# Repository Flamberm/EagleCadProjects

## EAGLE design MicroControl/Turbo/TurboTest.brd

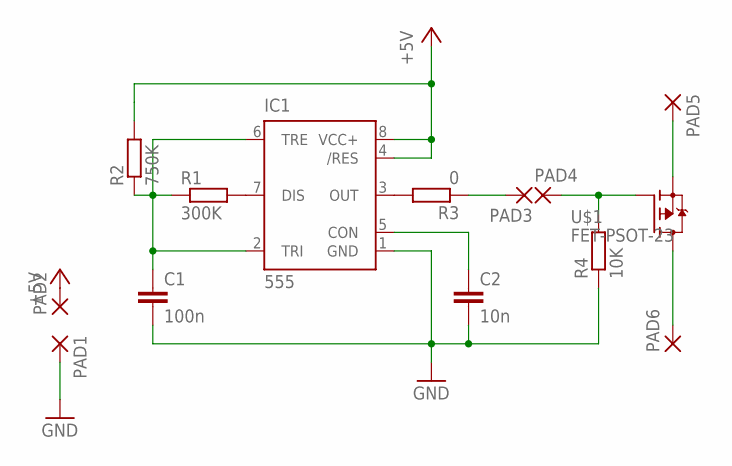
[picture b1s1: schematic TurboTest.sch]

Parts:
C1: 100n; CAP0805
C2: 10n; CAP0805
IC1: 555; SOIC-8
PAD1, PAD2, PAD3, PAD4, PAD5, PAD6: WIREPAD-SMD2; PAD-1.27X2.54
R1: 300K; RESC2012X50
R2: 750K; RESC2012X50
R3: 0; RESC2012X50
R4: 10K; RESC2012X50
U$1: FET-PSOT-23; SOT95P240X115-3

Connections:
+5V: IC1.4 (/RES), IC1.8 (VCC+), PAD2.P$1, R2.2
GND: C1.2, C2.2, IC1.1 (GND), PAD1.P$1, R4.1
unnamed: IC1.7 (DIS), R1.2
unnamed: C1.1, IC1.2 (TRI), IC1.6 (TRE), R1.1, R2.1
unnamed: C2.1, IC1.5 (CON)
unnamed: IC1.3 (OUT), R3.2
unnamed: PAD3.P$1, R3.1
unnamed: PAD4.P$1, R4.2, U$1.1 (G)
unnamed: PAD5.P$1, U$1.2 (S)
unnamed: PAD6.P$1, U$1.3 (D)

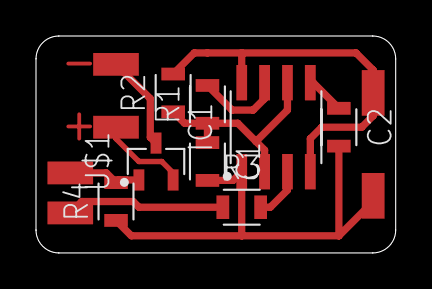
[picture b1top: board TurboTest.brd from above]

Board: 2 copper layers, 20.0 x 12.1 mm, 14 parts (0 on the bottom side), 10 nets.

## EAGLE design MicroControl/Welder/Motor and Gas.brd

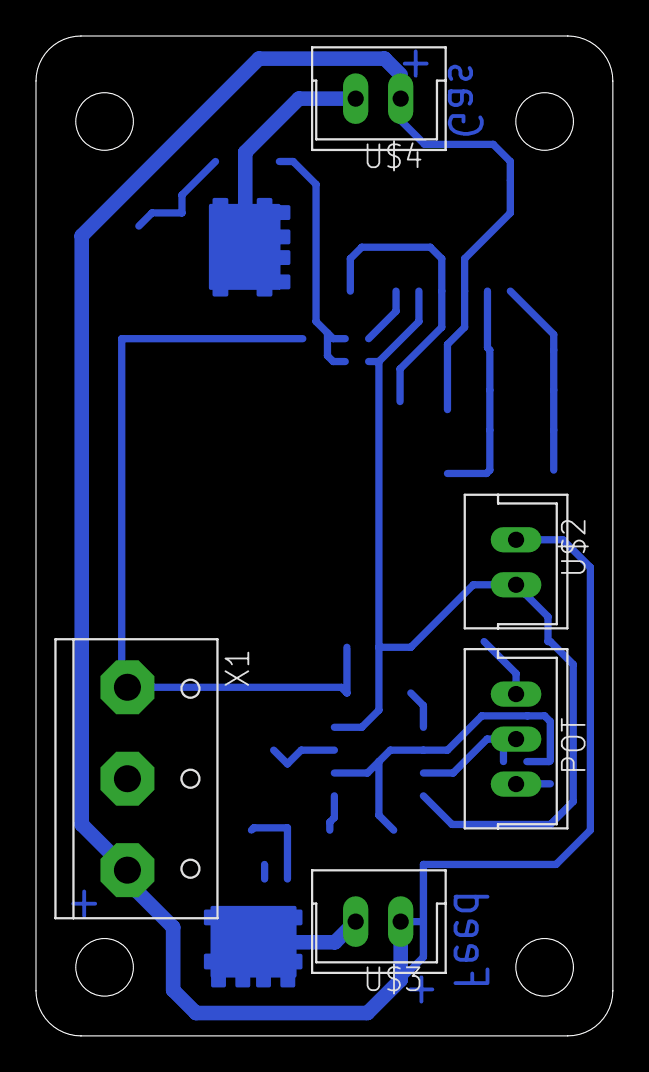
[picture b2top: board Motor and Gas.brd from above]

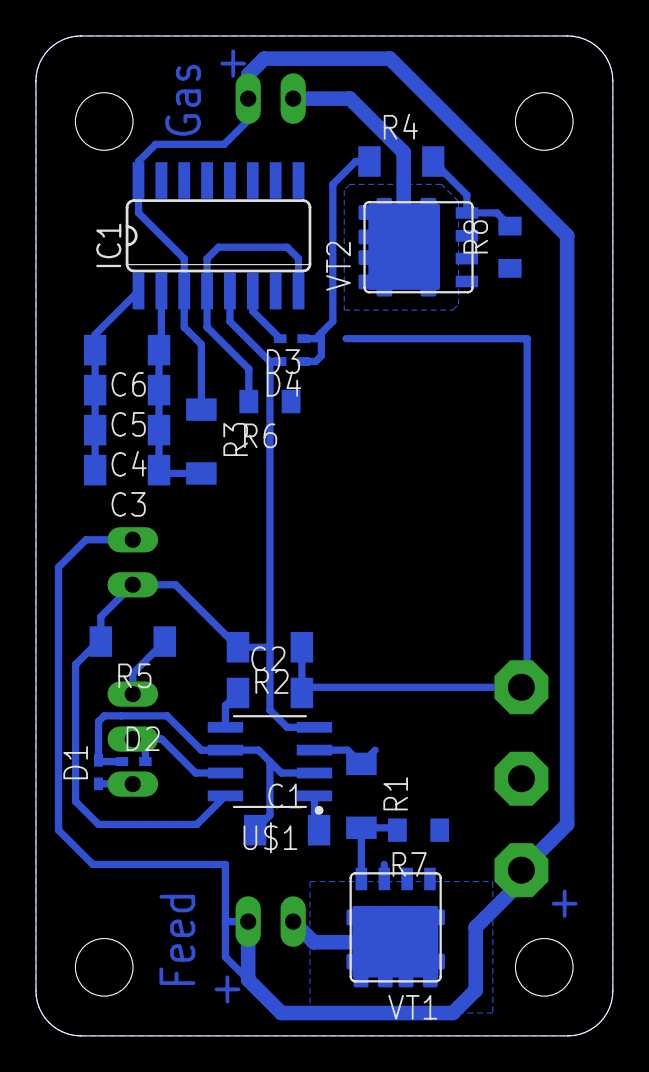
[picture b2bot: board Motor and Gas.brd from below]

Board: 2 copper layers, 32.0 x 55.5 mm, 27 parts (22 on the bottom side), 18 nets.

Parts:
C1: 1n; C1206
C2, C3, C4, C5, C6: 1u; C1206
D1, D2, D3, D4: SOD523
IC1: 4098D; SO16
POT: CON-XH-03; XH-03
R1, R4: 51R; R1206
R2: 10k; R1206
R3: 1M; R1206
R5: 390R; R1206
R6: R0805
R7, R8: 1K; R0805
U$1: IC-555SO-8; SOIC127P600X175-8
U$2, U$3, U$4: CON-XH-02; XH-02
VT1, VT2: POWERFLAT-5X6
X1: CON-5.08-03P; MKDSN1,5/3-5,08

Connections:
+12V: IC1.3, IC1.16, R3.1, U$2.1, U$3.1, U$4.1, X1.3
GND: C1.2, C2.2, R2.1, R6.1, R7.1, R8.1, U$1.1, VT1.S1, VT1.S2, VT1.S3, VT2.S1, VT2.S2, VT2.S3, X1.1
unnamed: U$3.2, VT1.D1
unnamed: C1.1, D1.A, D2.C, U$1.2, U$1.6
unnamed: C2.1, U$1.5
unnamed: D2.A, POT.2, U$1.7
unnamed: D1.C, POT.3
unnamed: POT.1, R5.1
unnamed: R1.1, U$1.3
unnamed: R1.2, R7.2, VT1.G
unnamed: D4.A, IC1.5, R2.2, R5.2, U$1.4, U$1.8, U$2.2
unnamed: C3.2, C4.2, C5.2, C6.2, IC1.1
unnamed: C3.1, C4.1, C5.1, C6.1, IC1.2, R3.2
unnamed: D3.A, IC1.6
unnamed: R4.2, R8.2, VT2.G
unnamed: IC1.4, IC1.8, R6.2
unnamed: U$4.2, VT2.D1
unnamed: D3.C, D4.C, R4.1

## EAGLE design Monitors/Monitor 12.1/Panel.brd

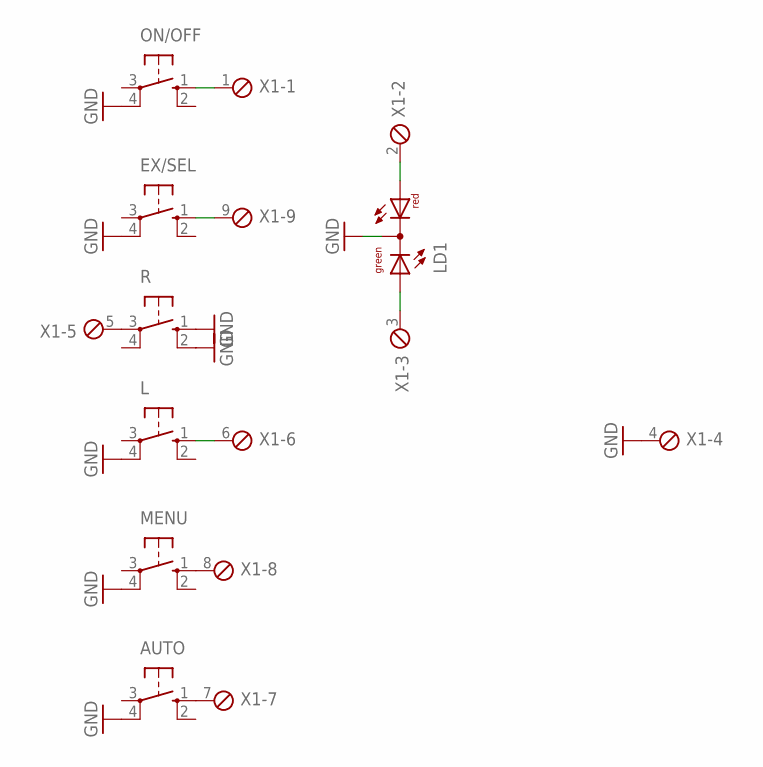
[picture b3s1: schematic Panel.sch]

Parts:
AUTO: 10-XX; B3F-10XX
EX/SEL: 10-XX; B3F-10XX
L: 10-XX; B3F-10XX
LD1: DUOLED-RG-C; DUOLED-C-5MM
MENU: 10-XX; B3F-10XX
ON/OFF: 10-XX; B3F-10XX
R: 10-XX; B3F-10XX
X1: MPT9; 9POL254

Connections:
GND: AUTO.4 (P1), EX/SEL.4 (P1), L.4 (P1), LD1.C, MENU.4 (P1), ON/OFF.4 (P1), R.1 (S), R.2 (S1), X1.4
unnamed: ON/OFF.1 (S), X1.1
unnamed: LD1.AR, X1.2
unnamed: LD1.AX (AG), X1.3
unnamed: EX/SEL.1 (S), X1.9
unnamed: R.3, X1.5
unnamed: L.1 (S), X1.6
unnamed: MENU.1 (S), X1.8
unnamed: AUTO.1 (S), X1.7

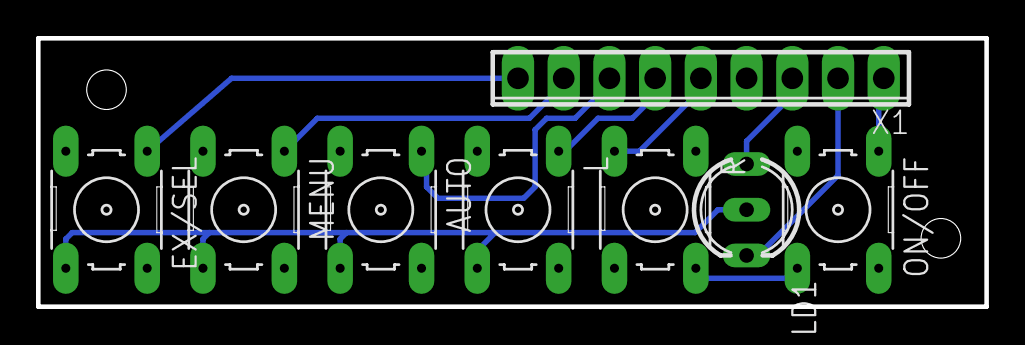
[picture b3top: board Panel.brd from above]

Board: 2 copper layers, 52.7 x 14.9 mm, 8 parts (0 on the bottom side), 9 nets.

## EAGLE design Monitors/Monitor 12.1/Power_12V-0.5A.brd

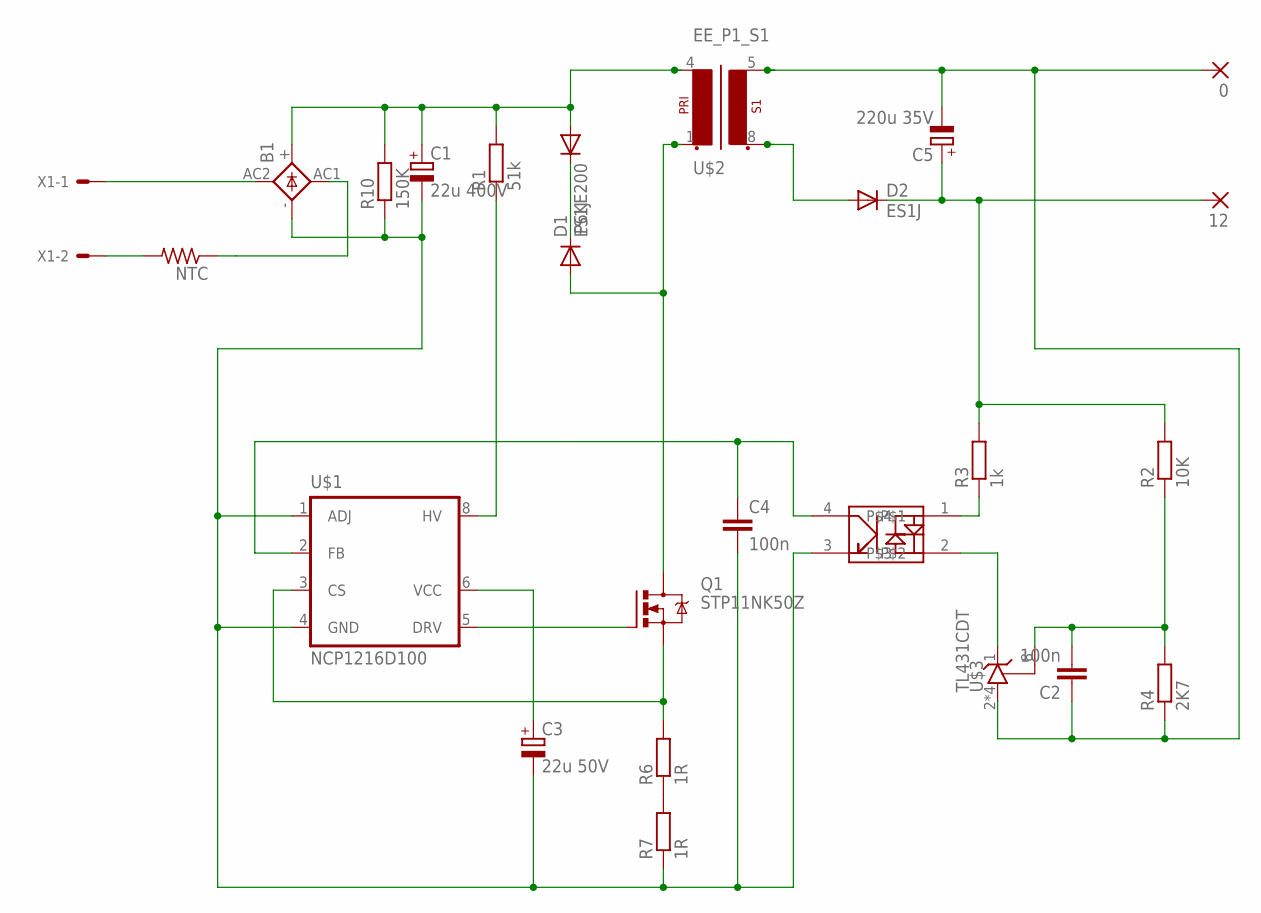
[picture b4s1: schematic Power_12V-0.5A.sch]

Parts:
0, 12: 2,54/0,8
B1: KBL
C1: 22u 400V; E5-13
C2, C4: 100n; C1206
C3: 22u 50V; E2,5-5
C5: 220u 35V; E2,5-7
D1, D2: ES1J; DO-214AC
NTC: R-US_0207/10; 0207/10
P6KE200: DIODE-SMB; SMB
Q1: STP11NK50Z; TO220BV
R1: 51k; 0922/22
R2: 10K; R1206
R3: 1k; R1206
R4: 2K7; R1206
R6, R7: 1R; R1206
R10: 150K; 0204/7
U$1: NCP1216D100; SOP8
U$2: EE_P1_S1; EE25_P1_S1
U$3: TL431CDT; SO8
U$5: EL3H4(TA)-VG; SSOP4
X1: KK-156-2

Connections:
unnamed: NTC.2, X1.2
unnamed: B1.AC2 (AC1), X1.1
unnamed: B1.AC1 (AC2), NTC.1
unnamed: R6.1, R7.2
unnamed: C4.1, U$1.2 (FB), U$5.4
unnamed: B1.+, C1.+, P6KE200.A, R1.2, R10.2, U$2.4 (P1-2)
unnamed: D1.C, P6KE200.C
unnamed: D1.A, Q1.D, U$2.1 (P1-1)
unnamed: C2.2, R2.1, R4.2, U$3.8 (R)
unnamed: R1.1, U$1.8 (HV)
unnamed: Q1.G, U$1.5 (DRV)
unnamed: Q1.S, R6.2, U$1.3 (CS)
unnamed: R3.1, U$5.1
unnamed: C3.+, U$1.6 (VCC)
unnamed: U$3.1 (C), U$5.2
unnamed: B1.-, C1.-, C3.-, C4.2, R7.1, R10.1, U$1.1 (ADJ), U$1.4 (GND), U$5.3
unnamed: 0.1, C2.1, C5.-, R4.1, U$2.5 (S1-2), U$3.2 (A), U$3.3 (A), U$3.6 (A), U$3.7 (A)
unnamed: 12.1, C5.+, D2.C, R2.2, R3.2
unnamed: D2.A, U$2.8 (S1-1)

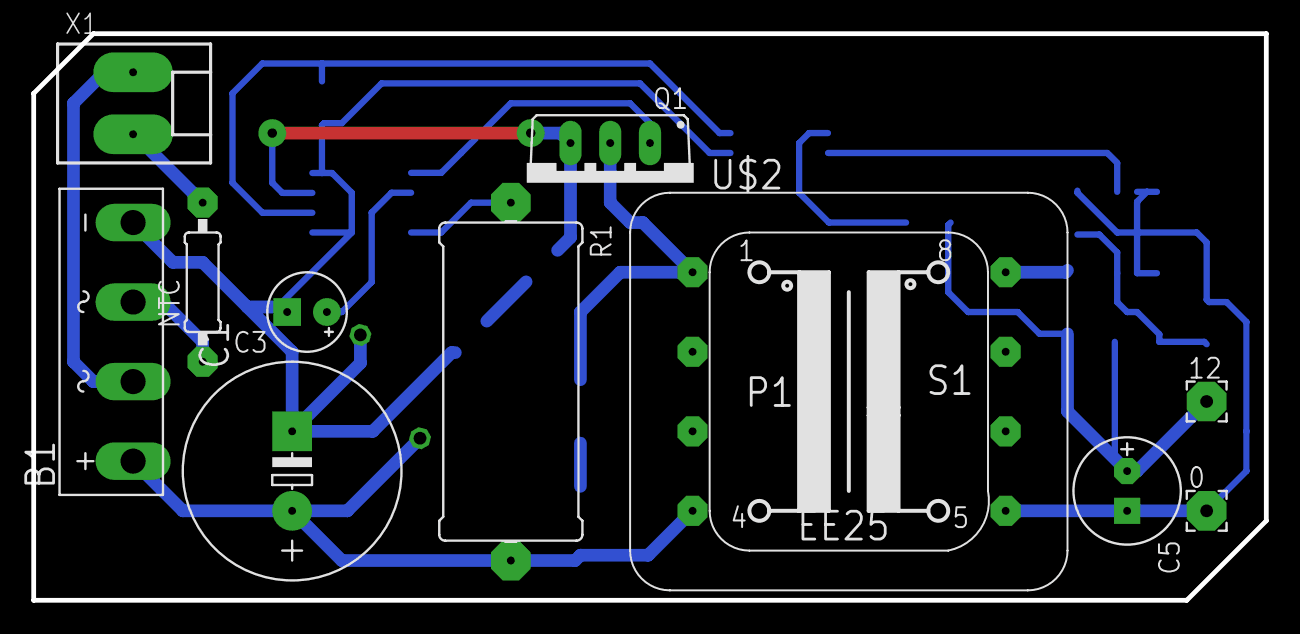
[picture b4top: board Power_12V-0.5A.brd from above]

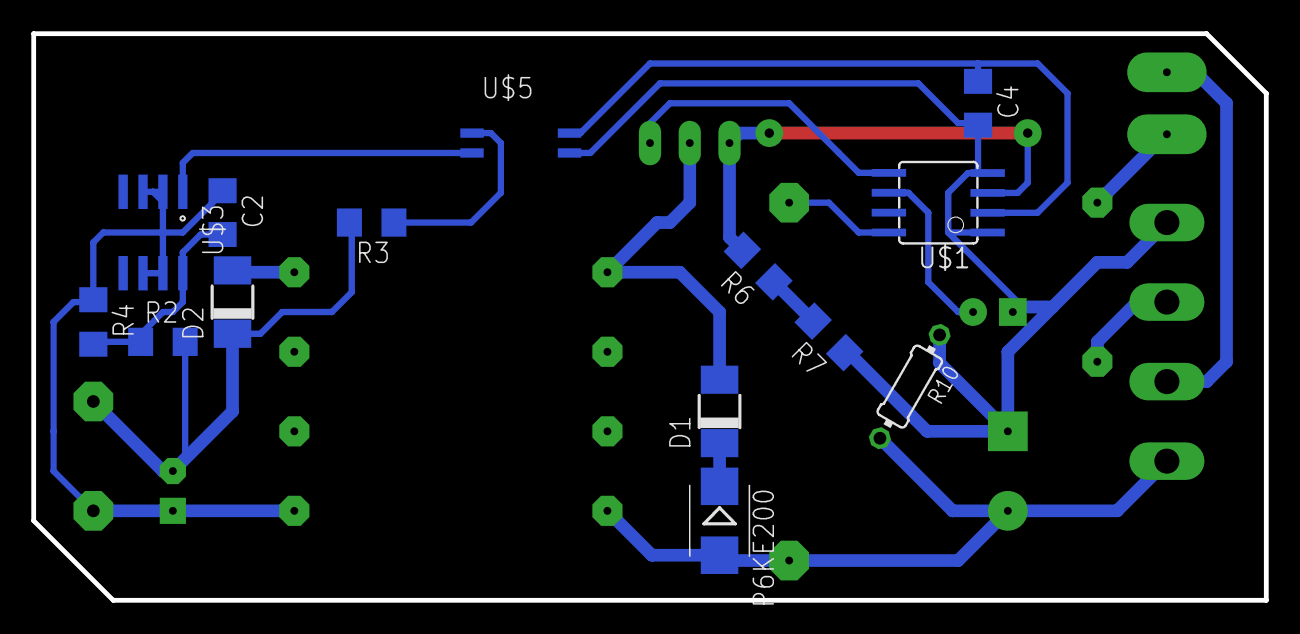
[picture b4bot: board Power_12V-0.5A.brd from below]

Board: 2 copper layers, 78.7 x 36.2 mm, 25 parts (14 on the bottom side), 19 nets.

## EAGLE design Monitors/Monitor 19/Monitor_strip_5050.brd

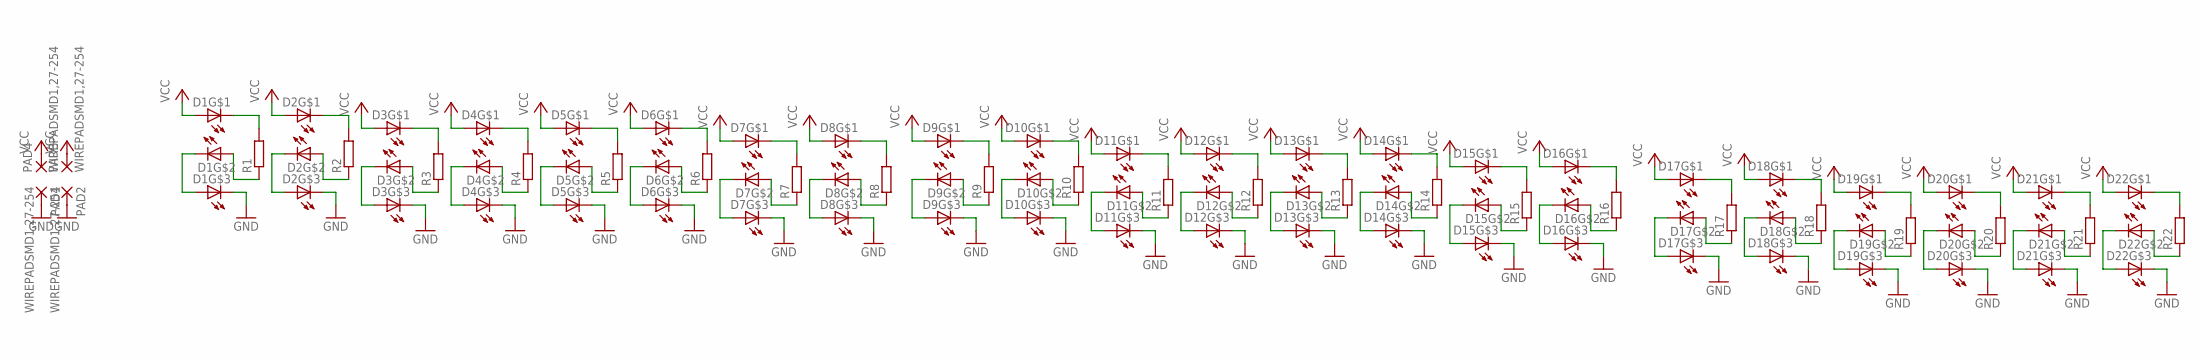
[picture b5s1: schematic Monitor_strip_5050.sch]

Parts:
D1, D2, D3, D4, D5, D6, D7, D8, D9, D10, D11, D12, D13, D14, D15, D16, D17, D18, D19, D20, D21, D22: LED5050_SEPARATES; LED505_SMALLPADS
PAD1, PAD2, PAD3, PAD4: WIREPADSMD1,27-254; SMD1,27-2,54
R1, R2, R3, R4, R5, R6, R7, R8, R9, R10, R11, R12, R13, R14, R15, R16, R17, R18, R19, R20, R21, R22: R-EU_R0805; R0805

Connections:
GND: D1.P$3 (C), D2.P$3 (C), D3.P$3 (C), D4.P$3 (C), D5.P$3 (C), D6.P$3 (C), D7.P$3 (C), D8.P$3 (C), D9.P$3 (C), D10.P$3 (C), D11.P$3 (C), D12.P$3 (C), D13.P$3 (C), D14.P$3 (C), D15.P$3 (C), D16.P$3 (C), D17.P$3 (C), D18.P$3 (C), D19.P$3 (C), D20.P$3 (C), D21.P$3 (C), D22.P$3 (C), PAD1.1, PAD2.1
unnamed: D1.P$1 (C), R1.2
unnamed: D1.P$5 (A), R1.1
unnamed: D2.P$2 (C), D2.P$4 (A)
unnamed: D2.P$1 (C), R2.2
unnamed: D2.P$5 (A), R2.1
unnamed: D3.P$2 (C), D3.P$4 (A)
unnamed: D3.P$1 (C), R3.2
unnamed: D3.P$5 (A), R3.1
unnamed: D4.P$2 (C), D4.P$4 (A)
unnamed: D1.P$2 (C), D1.P$4 (A)
unnamed: D4.P$1 (C), R4.2
unnamed: D4.P$5 (A), R4.1
unnamed: D5.P$2 (C), D5.P$4 (A)
unnamed: D5.P$1 (C), R5.2
unnamed: D5.P$5 (A), R5.1
unnamed: D6.P$2 (C), D6.P$4 (A)
unnamed: D6.P$1 (C), R6.2
unnamed: D6.P$5 (A), R6.1
unnamed: D7.P$2 (C), D7.P$4 (A)
unnamed: D7.P$1 (C), R7.2
unnamed: D7.P$5 (A), R7.1
unnamed: D8.P$2 (C), D8.P$4 (A)
unnamed: D8.P$1 (C), R8.2
unnamed: D8.P$5 (A), R8.1
unnamed: D9.P$2 (C), D9.P$4 (A)
unnamed: D9.P$1 (C), R9.2
unnamed: D9.P$5 (A), R9.1
unnamed: D10.P$2 (C), D10.P$4 (A)
unnamed: D10.P$1 (C), R10.2
unnamed: D10.P$5 (A), R10.1
unnamed: D11.P$2 (C), D11.P$4 (A)
unnamed: D11.P$1 (C), R11.2
unnamed: D11.P$5 (A), R11.1
unnamed: D12.P$2 (C), D12.P$4 (A)
unnamed: D12.P$1 (C), R12.2
unnamed: D12.P$5 (A), R12.1
unnamed: D13.P$2 (C), D13.P$4 (A)
unnamed: D13.P$1 (C), R13.2
unnamed: D13.P$5 (A), R13.1
unnamed: D14.P$2 (C), D14.P$4 (A)
unnamed: D14.P$1 (C), R14.2
unnamed: D14.P$5 (A), R14.1
unnamed: D15.P$2 (C), D15.P$4 (A)
unnamed: D15.P$1 (C), R15.2
unnamed: D15.P$5 (A), R15.1
unnamed: D16.P$2 (C), D16.P$4 (A)
unnamed: D16.P$1 (C), R16.2
unnamed: D16.P$5 (A), R16.1
unnamed: D17.P$2 (C), D17.P$4 (A)
unnamed: D17.P$1 (C), R17.2
unnamed: D17.P$5 (A), R17.1
unnamed: D18.P$2 (C), D18.P$4 (A)
unnamed: D18.P$1 (C), R18.2
unnamed: D18.P$5 (A), R18.1
unnamed: D19.P$2 (C), D19.P$4 (A)
unnamed: D19.P$1 (C), R19.2
unnamed: D19.P$5 (A), R19.1
unnamed: D20.P$2 (C), D20.P$4 (A)
unnamed: D20.P$1 (C), R20.2
unnamed: D20.P$5 (A), R20.1
unnamed: D21.P$2 (C), D21.P$4 (A)
unnamed: D21.P$1 (C), R21.2
unnamed: D21.P$5 (A), R21.1
unnamed: D22.P$2 (C), D22.P$4 (A)
unnamed: D22.P$1 (C), R22.2
unnamed: D22.P$5 (A), R22.1
VCC: D1.P$6 (A), D2.P$6 (A), D3.P$6 (A), D4.P$6 (A), D5.P$6 (A), D6.P$6 (A), D7.P$6 (A), D8.P$6 (A), D9.P$6 (A), D10.P$6 (A), D11.P$6 (A), D12.P$6 (A), D13.P$6 (A), D14.P$6 (A), D15.P$6 (A), D16.P$6 (A), D17.P$6 (A), D18.P$6 (A), D19.P$6 (A), D20.P$6 (A), D21.P$6 (A), D22.P$6 (A), PAD3.1, PAD4.1

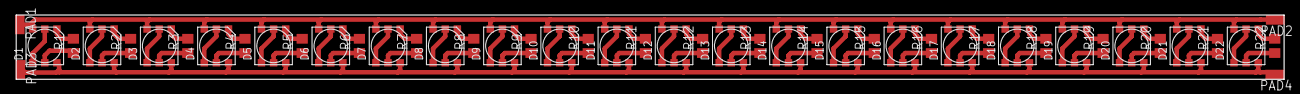
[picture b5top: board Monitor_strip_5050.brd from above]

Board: 2 copper layers, 168.9 x 8.6 mm, 48 parts (0 on the bottom side), 68 nets.

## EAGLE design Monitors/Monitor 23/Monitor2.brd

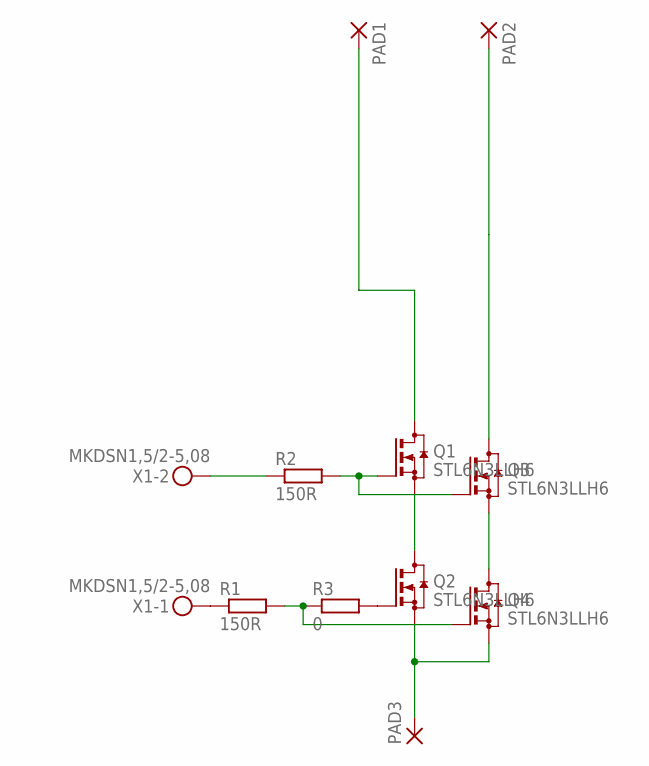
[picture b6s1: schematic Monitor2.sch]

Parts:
PAD1, PAD2, PAD3: 3,81/1,4
Q1, Q2, Q3, Q4: STL6N3LLH6; POWERFLAT-2X2
R1, R2: 150R; R1206
R3: 0; R1206
X1: MKDSN1,5/2-5,08

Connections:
unnamed: Q1.4S (S), Q1.S, Q2.1D (D), Q2.2D (D), Q2.5D (D), Q2.6D (D), Q2.D
unnamed: Q2.3G (G), R3.2
unnamed: Q1.3G (G), Q3.3G (G), R2.2
unnamed: PAD1.1, Q1.1D (D), Q1.2D (D), Q1.5D (D), Q1.6D (D), Q1.D
unnamed: PAD3.1, Q2.4S (S), Q2.S, Q4.4S (S), Q4.S
unnamed: R2.1, X1.2
unnamed: R1.1, X1.1
unnamed: Q4.3G (G), R1.2, R3.1
unnamed: PAD2.1, Q3.1D (D), Q3.2D (D), Q3.5D (D), Q3.6D (D), Q3.D
unnamed: Q3.4S (S), Q3.S, Q4.1D (D), Q4.2D (D), Q4.5D (D), Q4.6D (D), Q4.D

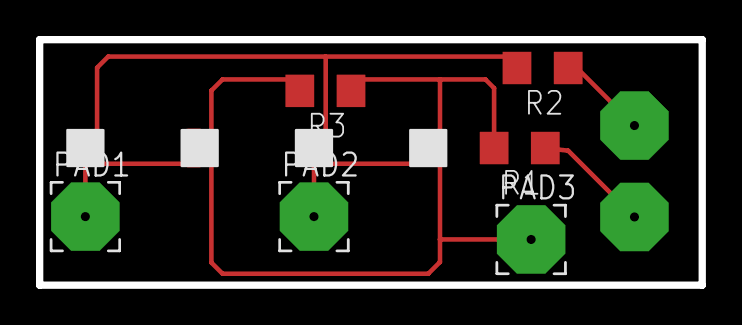
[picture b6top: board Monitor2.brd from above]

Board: 2 copper layers, 36.8 x 13.6 mm, 11 parts (1 on the bottom side), 10 nets.

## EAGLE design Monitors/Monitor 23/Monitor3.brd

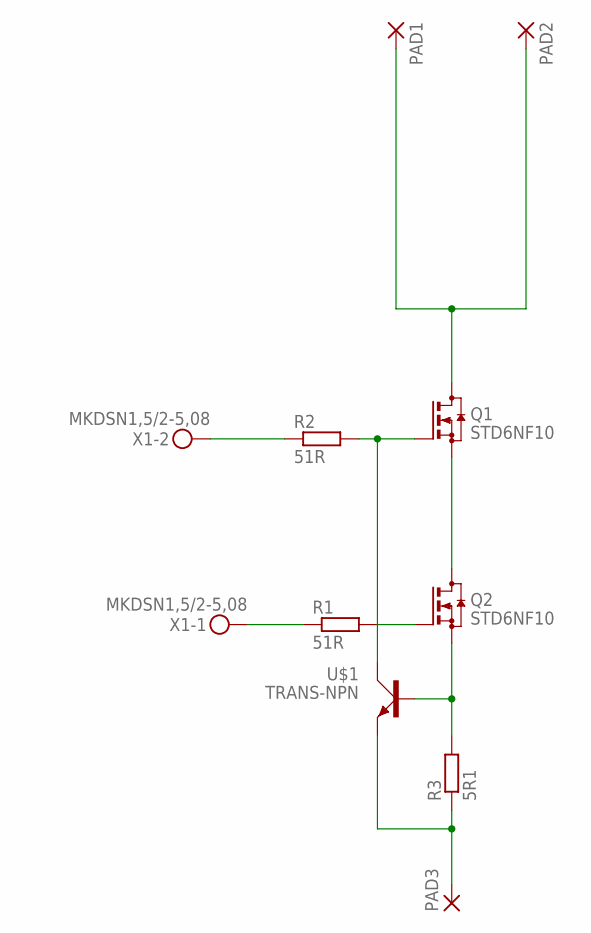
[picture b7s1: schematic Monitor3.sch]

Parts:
PAD1, PAD2, PAD3: 3,81/1,4
Q1, Q2: STD6NF10; DPAK
R1, R2: 51R; R0805
R3: 5R1; R0805
U$1: TRANS-NPN; SOT-92WIDE
X1: MKDSN1,5/2-5,08

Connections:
unnamed: Q1.S, Q2.D
unnamed: Q2.G, R1.2
unnamed: Q1.G, R2.2, U$1.C
unnamed: PAD1.1, PAD2.1, Q1.D
unnamed: R2.1, X1.2
unnamed: R1.1, X1.1
unnamed: Q2.S, R3.2, U$1.B
unnamed: PAD3.1, R3.1, U$1.E

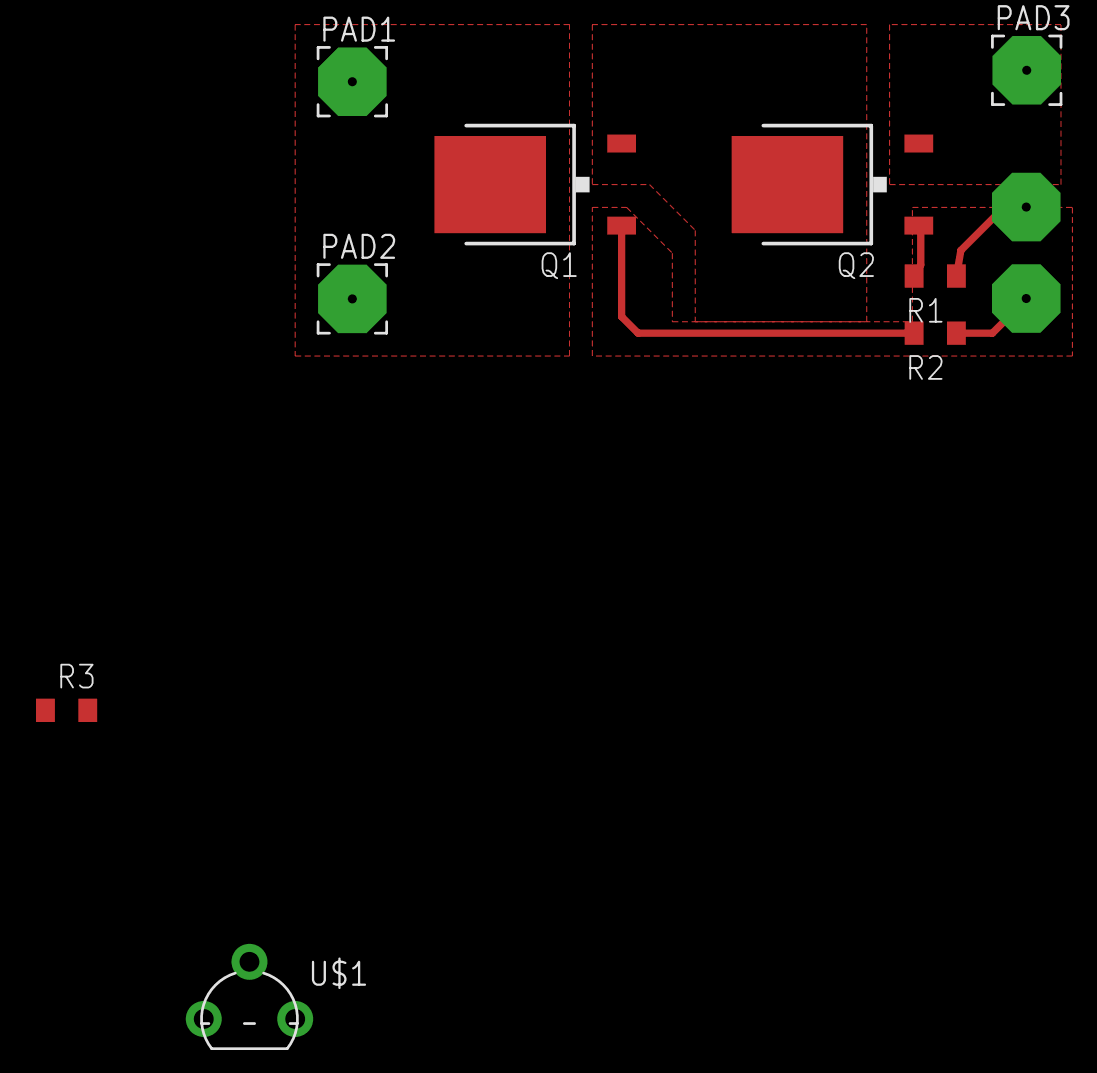
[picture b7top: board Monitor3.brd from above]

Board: 2 copper layers, 10 parts (1 on the bottom side), 8 nets.

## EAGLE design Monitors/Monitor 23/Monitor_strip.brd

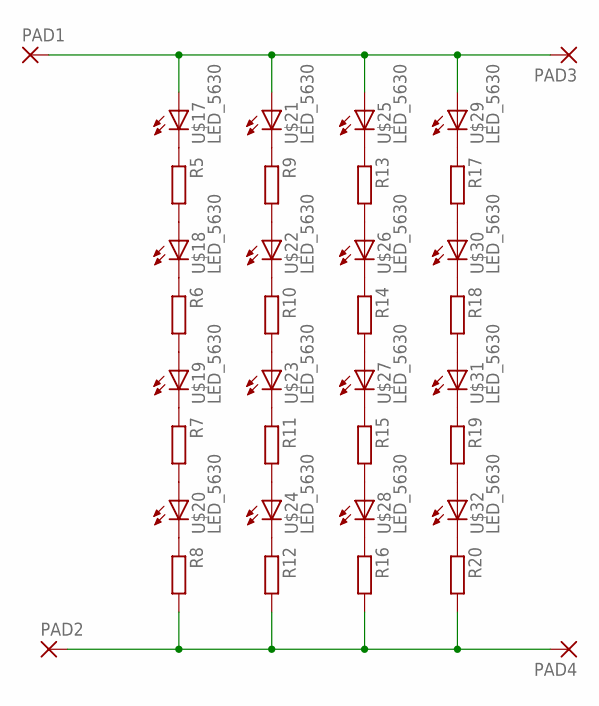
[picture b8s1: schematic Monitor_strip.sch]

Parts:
PAD1, PAD2, PAD3, PAD4: SMD2; SMD1,27-2,54
R5, R6, R7, R8, R9, R10, R11, R12, R13, R14, R15, R16, R17, R18, R19, R20: R_0805; R0805
U$17, U$18, U$19, U$20, U$21, U$22, U$23, U$24, U$25, U$26, U$27, U$28, U$29, U$30, U$31, U$32: LED_5630; LED5730

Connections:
unnamed: R5.1, U$17.C
unnamed: R6.1, U$18.C
unnamed: R7.1, U$19.C
unnamed: R8.1, U$20.C
unnamed: R6.2, U$19.A, U$19.A1 (A)
unnamed: R7.2, U$20.A, U$20.A1 (A)
unnamed: R5.2, U$18.A, U$18.A1 (A)
unnamed: R9.1, U$21.C
unnamed: R10.1, U$22.C
unnamed: R11.1, U$23.C
unnamed: R12.1, U$24.C
unnamed: R10.2, U$23.A, U$23.A1 (A)
unnamed: R11.2, U$24.A, U$24.A1 (A)
unnamed: R9.2, U$22.A, U$22.A1 (A)
unnamed: R13.1, U$25.C
unnamed: R14.1, U$26.C
unnamed: R15.1, U$27.C
unnamed: R16.1, U$28.C
unnamed: R14.2, U$27.A, U$27.A1 (A)
unnamed: R15.2, U$28.A, U$28.A1 (A)
unnamed: R13.2, U$26.A, U$26.A1 (A)
unnamed: R17.1, U$29.C
unnamed: R18.1, U$30.C
unnamed: R19.1, U$31.C
unnamed: R20.1, U$32.C
unnamed: R18.2, U$31.A, U$31.A1 (A)
unnamed: R19.2, U$32.A, U$32.A1 (A)
unnamed: R17.2, U$30.A, U$30.A1 (A)
unnamed: PAD1.1, PAD3.1, U$17.A, U$17.A1 (A), U$21.A, U$21.A1 (A), U$25.A, U$25.A1 (A), U$29.A, U$29.A1 (A)
unnamed: PAD2.1, PAD4.1, R8.2, R12.2, R16.2, R20.2

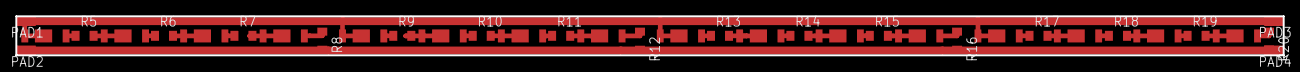
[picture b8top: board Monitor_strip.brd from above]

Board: 2 copper layers, 165.1 x 5.1 mm, 36 parts (0 on the bottom side), 30 nets.
